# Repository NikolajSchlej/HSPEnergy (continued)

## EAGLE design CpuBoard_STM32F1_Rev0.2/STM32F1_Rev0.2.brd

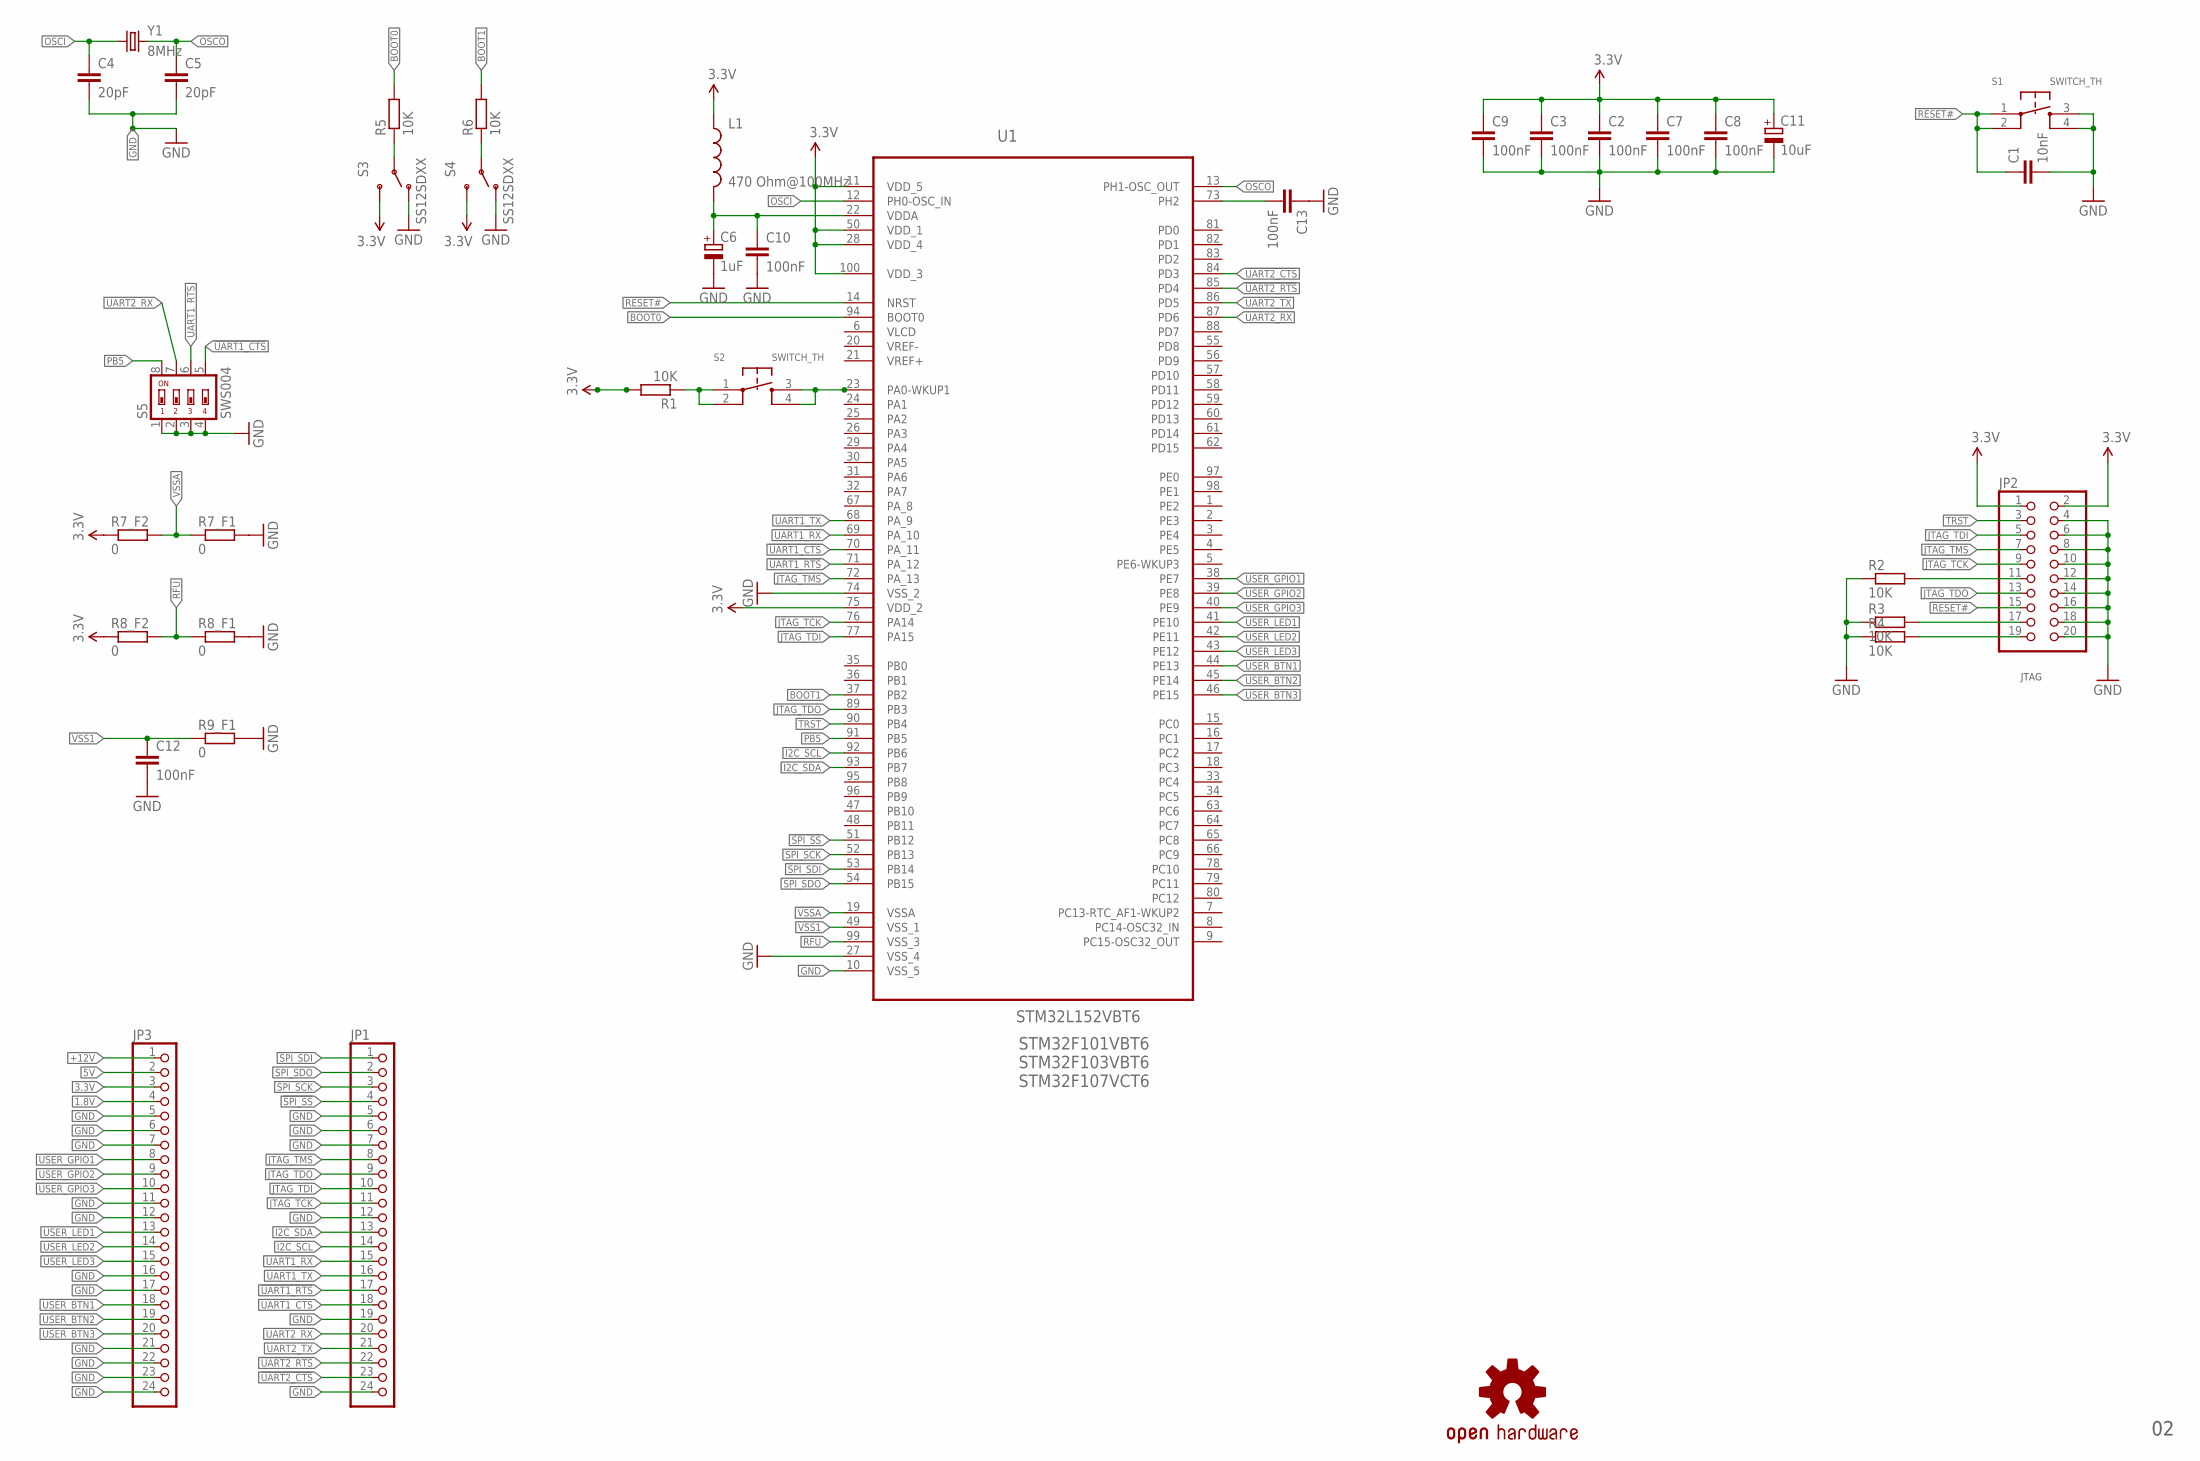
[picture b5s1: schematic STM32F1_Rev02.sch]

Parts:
C1: 10nF; C0805K
C2, C3, C7, C8, C9, C10, C12, C13: 100nF; C0805K
C4, C5: 20pF; C0805K
C6: 1uF; PANASONIC_B
C11: 10uF; PANASONIC_B
JP1, JP3: PINHD-1X24; 1X24
JP2: PINHD-2X10; 2X10
L1: 470 Ohm@100MHz; 0805
R1, R2, R3, R4, R5, R6: 10K; R0805
R7_F1, R7_F2, R8_F1, R8_F2, R9_F1: 0; R0805
S1, S2: SWITCH_TH; SWITCH_TROUGHHOLE
S3, S4: SS12SDXX
S5: SWS004; SMS-004
U1: STM32L152VBT6; QFP50P1600X1600X160-100N
U$1: OSHW-LOGOS; OSHW-LOGO-S
Y1: 8MHz; HC49UP

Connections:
1.8V: JP3.4
3.3V: C2.1, C3.1, C7.1, C8.1, C9.1, C11.+, JP2.1, JP2.2, JP3.3, L1.1, R1.2, R7_F2.1, R8_F2.1, S3.3, S4.3, U1.11 (VDD_5), U1.28 (VDD_4), U1.50 (VDD_1), U1.75 (VDD_2), U1.100 (VDD_3)
5V: JP3.2
!SPI_SS: JP1.4, U1.51 (PB12)
!UART1_CTS: JP1.18, S5.5, U1.70 (PA_11)
!UART1_RTS: JP1.17, S5.6, U1.71 (PA_12)
!UART2_CTS: JP1.23, U1.84 (PD3)
!UART2_RTS: JP1.22, U1.85 (PD4)
+12V: JP3.1
BOOT0: R5.2, U1.94 (BOOT0)
BOOT1: R6.2, U1.37 (PB2)
GND: C1.2, C2.2, C3.2, C4.2, C5.2, C6.-, C7.2, C8.2, C9.2, C10.2, C11.-, C12.2, C13.1, JP1.5, JP1.6, JP1.7, JP1.12, JP1.19, JP1.24, JP2.4, JP2.6, JP2.8, JP2.10, JP2.12, JP2.14, JP2.16, JP2.18, JP2.20, JP3.5, JP3.6, JP3.7, JP3.11, JP3.12, JP3.16, JP3.17, JP3.21, JP3.22, JP3.23, JP3.24, R2.1, R3.1, R4.1, R7_F1.2, R8_F1.2, R9_F1.2, S1.3, S1.4, S3.1, S4.1, S5.1, S5.2, S5.3, S5.4, U1.10 (VSS_5), U1.27 (VSS_4), U1.74 (VSS_2)
I2C_SCL: JP1.14, U1.92 (PB6)
I2C_SDA: JP1.13, U1.93 (PB7)
JTAG_TCK: JP1.11, JP2.9, U1.76 (PA14)
JTAG_TDI: JP1.10, JP2.5, U1.77 (PA15)
JTAG_TDO: JP1.9, JP2.13, U1.89 (PB3)
JTAG_TMS: JP1.8, JP2.7, U1.72 (PA_13)
unnamed: C13.2, U1.73 (PH2)
unnamed: C6.+, C10.1, L1.2, U1.22 (VDDA)
unnamed: R1.1, S2.1, S2.2
unnamed: R5.1, S3.2
unnamed: R6.1, S4.2
unnamed: JP2.11, R2.2
unnamed: JP2.17, R3.2
unnamed: JP2.19, R4.2
OSCI: C4.1, U1.12 (PH0-OSC_IN), Y1.1
OSCO: C5.1, U1.13 (PH1-OSC_OUT), Y1.2
PA0: S2.3, S2.4, U1.23 (PA0-WKUP1)
PB5: S5.8, U1.91 (PB5)
RESET#: C1.1, JP2.15, S1.1, S1.2, U1.14 (NRST)
RFU: R8_F1.1, R8_F2.2, U1.99 (VSS_3)
SPI_SCK: JP1.3, U1.52 (PB13)
SPI_SDI: JP1.1, U1.53 (PB14)
SPI_SDO: JP1.2, U1.54 (PB15)
TRST: JP2.3, U1.90 (PB4)
UART1_RX: JP1.15, U1.69 (PA_10)
UART1_TX: JP1.16, U1.68 (PA_9)
UART2_RX: JP1.20, S5.7, U1.87 (PD6)
UART2_TX: JP1.21, U1.86 (PD5)
USER_BTN1: JP3.18, U1.44 (PE13)
USER_BTN2: JP3.19, U1.45 (PE14)
USER_BTN3: JP3.20, U1.46 (PE15)
USER_GPIO1: JP3.8, U1.38 (PE7)
USER_GPIO2: JP3.9, U1.39 (PE8)
USER_GPIO3: JP3.10, U1.40 (PE9)
USER_LED1: JP3.13, U1.41 (PE10)
USER_LED2: JP3.14, U1.42 (PE11)
USER_LED3: JP3.15, U1.43 (PE12)
VLCD: U1.6 (VLCD)
VSS1: C12.1, R9_F1.1, U1.49 (VSS_1)
VSSA: R7_F1.1, R7_F2.2, U1.19 (VSSA)

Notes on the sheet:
JTAG
STM32F101VBT6 STM32F103VBT6 STM32F107VCT6

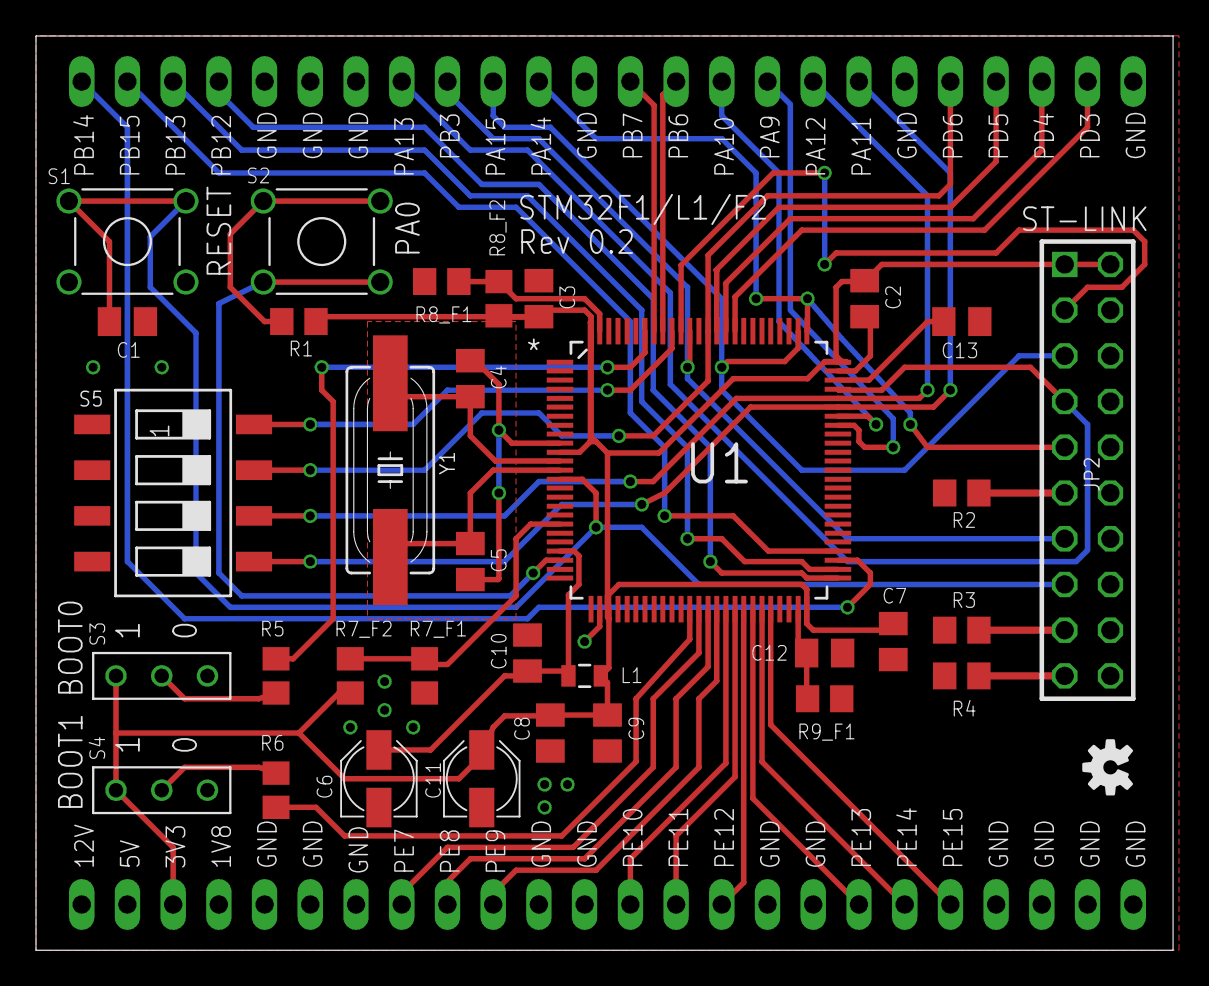
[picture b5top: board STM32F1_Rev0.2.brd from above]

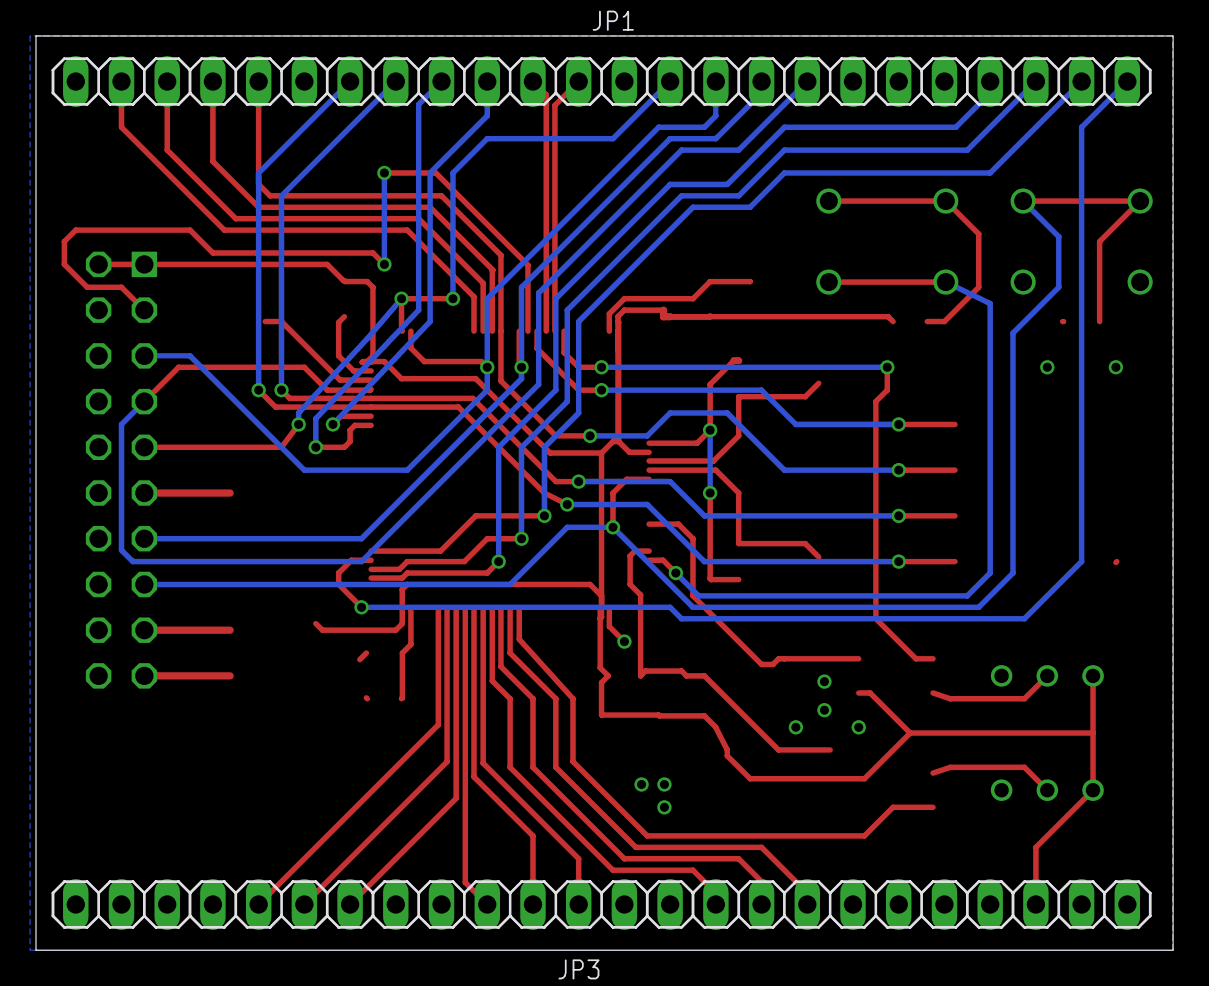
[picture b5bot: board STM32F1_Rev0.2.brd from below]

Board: 2 copper layers, 63.2 x 50.8 mm, 36 parts (2 on the bottom side), 48 nets.

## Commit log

2013-06-01 Project start
    CpuBoards for STM32F1xx/L1xx/F2xx and Infineon XE167FM
2013-06-01 Backup files removed
2013-06-01 Files renamed for consistency
2013-06-01 Visible bottom layer for STM32 board
2013-06-01 Missing GND pin description
2013-06-01 OSHW logo rotated
2013-06-02 Texts position slightly corrected
2013-06-24 Added designs made by Claudiu Covaci
    Added BaseBoard 0.1 and CPUBoard_PIC 0.1
2013-07-01 Base Board revision 0.2
    Added schematics of early version of BB 0.2
2013-07-03 Added shunt resistor for current measurement
    In case of no ammeter
